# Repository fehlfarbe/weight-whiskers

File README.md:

# weight-whiskers

This is an ESP32 S2 based smart scale that tracks my cat's weight and sends data via MQTT to my smart home. I did the project to automatically track my sick cat's weight when he visits his toilet. Unfortunately he died in August 2023. So this is dedicated to you, my beloved Schneeball 🖤🌈

Schneeball testing the scale

# Hardware

I made a prototype on a solder board with an ESP32 S2 breakout board. I like the WEMOS S2 mini which is very small. You might have to change some pins. Or just use the gerber files and make the PCB. You can find the KiCAD project and gerber files at [hardware](hardware/).

You can connect all load cells that are compatible with the HX711 IC. I'm using [four cells that can measure up to 50Kg](https://de.aliexpress.com/item/1005004867068245.html) because it's easier to keep a big cat toilet balanced.

## Schematic

[PDF](doc/pcb_schematic.pdf)

## 2D plot

#### Front

**Important:** Check the VCC and GND position of the display! Some displays have GND on the first pin and VCC on the second like in the rendered image. You need a display with `VCC  | GND | SCL | SDA` pinout as you can see in the 2D front plot.

#### Back

## 3D rendering

#### Front

#### Back

## Images

# Software

## Installation

Just install [PlatformIO](https://platformio.org/), clone the project, connect the device and run:
`pio run -t upload -e esp32s` to upload the sketch and `pio run -t uploadfs -e esp32s2` to upload the filesystem that contains the config file and web interface. Use the environment `-e esp32s2_ota` if you want to update the device via WiFi.
WARNING: When you update the filesystem you will overwrite the config file and measurements. So please backup it first!

# Usage

On first start the weight-whiskers scale will create an access point that has a config page at <http://192.168.4.1> where you can connect to your local WiFi. If the connection was successful you can find the actual web interface at <http://weight-whiskers.local> in your local network or check your internet router page to get the local IP address.

With a long press on the encoder you can calibrate the load cells with a known weight. The default weight is 500g but you can change it by rotating the encoder (or set it up on the web interface). Just follow the instructions on the display. To tare the scale just short press (<1s) the encoder button.

You can configure the `scale minimum weight` on the web interface. If the cat enters the scale, the LED lights up yellow and the scale measures the weight (with standard deviation) and duration until the cat left the scale. Afterwards the LED lights up green and the result will be stored in the CSV file and sent via MQTT message. If you connected the buzzer, a fancy sound will be played :D

## Web interface

On the web interface you can show, delete and down- and upload the data. The measurements are stored in a CSV file on the device. You can download it and open it in a text editor or import it with a spreadsheet editor. You can also edit the config and show the scale's live data.

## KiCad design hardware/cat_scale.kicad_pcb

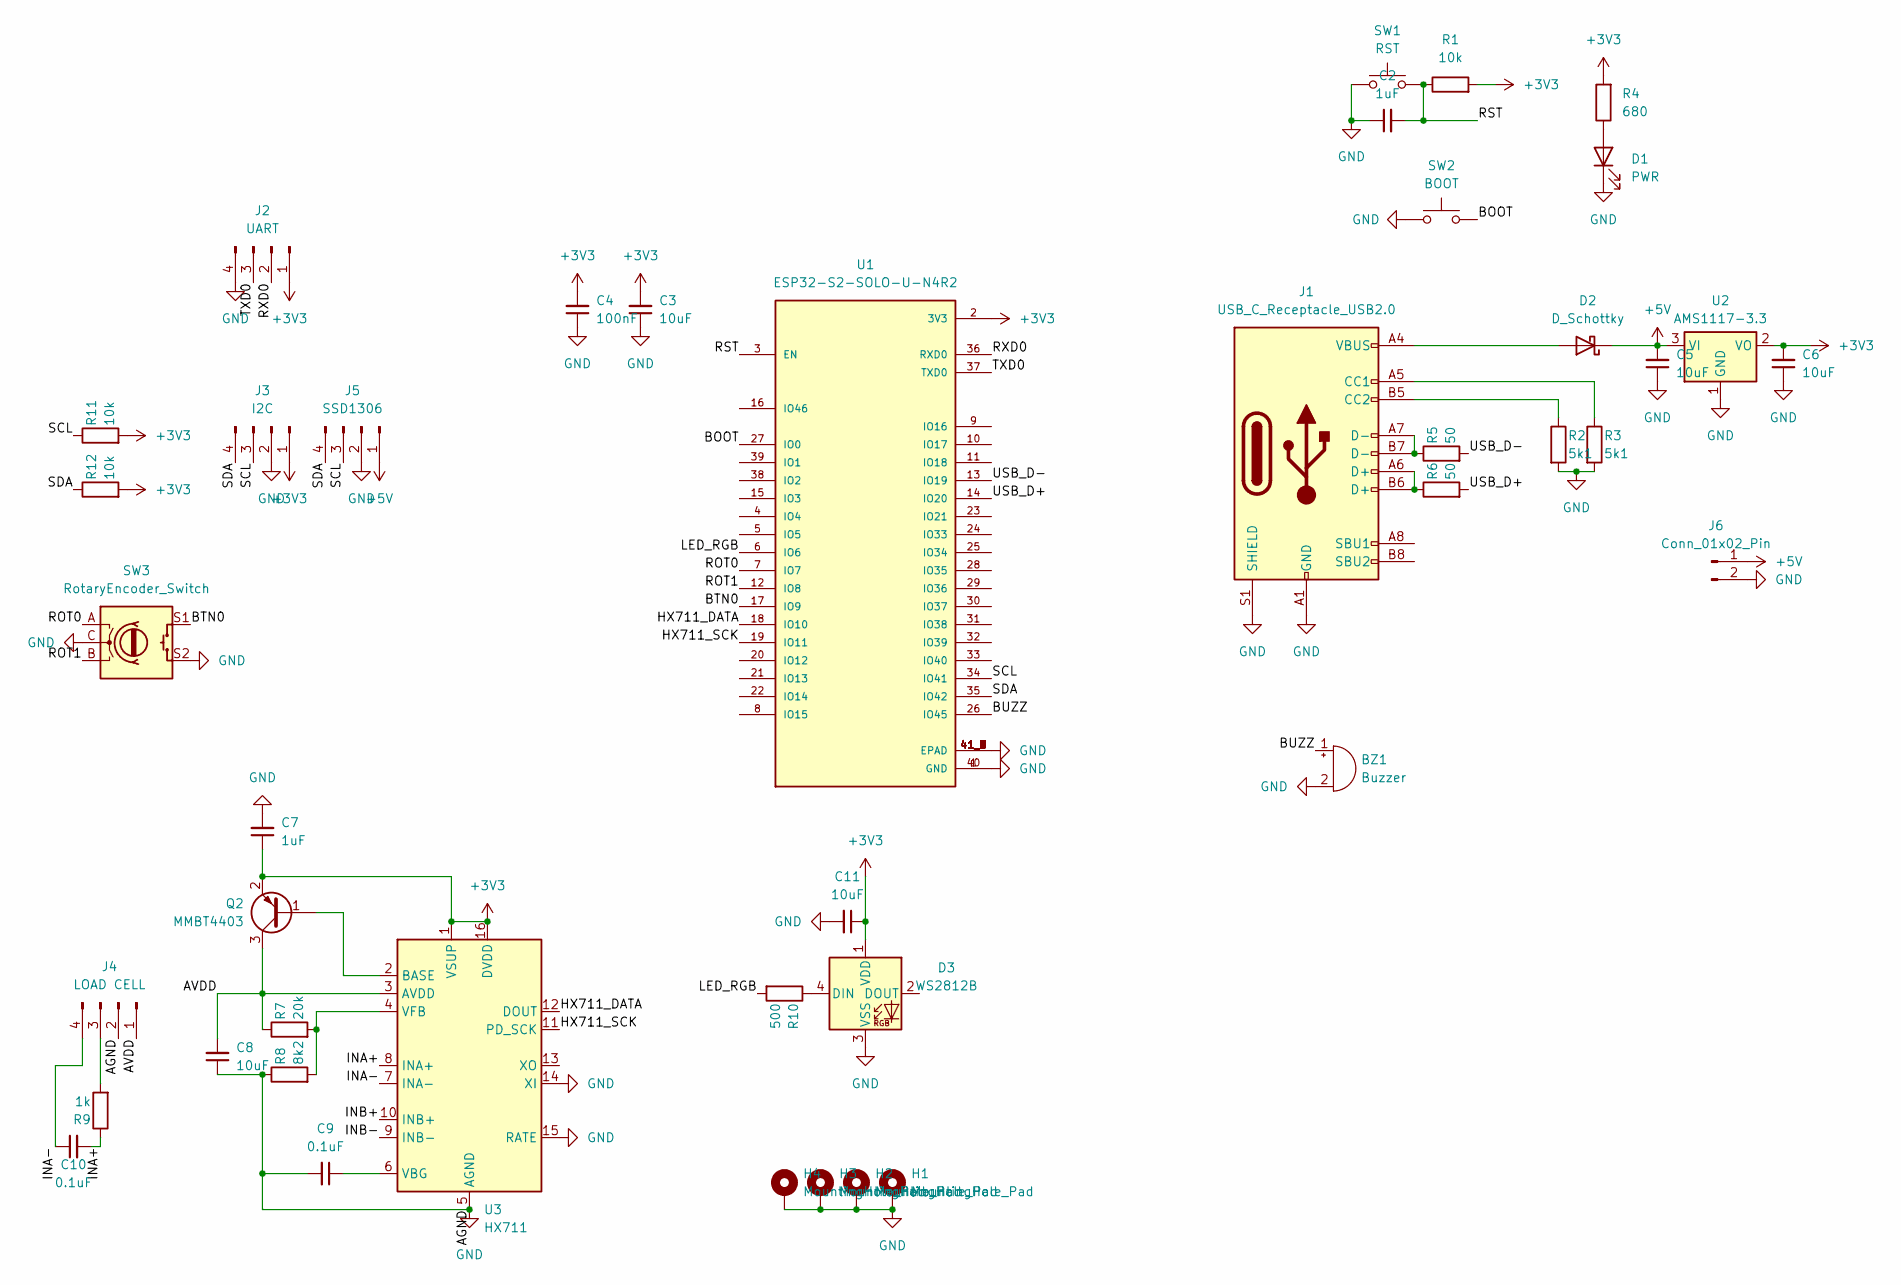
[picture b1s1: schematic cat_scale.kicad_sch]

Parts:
BZ1: Buzzer; Buzzer_Murata_PKMCS0909E
C2, C7: 1uF; C_1206_3216Metric
C3, C5, C6, C8, C11: 10uF; C_1206_3216Metric
C4: 100nF; C_1206_3216Metric
C9, C10: 0.1uF; C_1206_3216Metric
D1: PWR; LED_0805_2012Metric
D2: D_Schottky; D_SOD-323
D3: WS2812B; LED_WS2812B_PLCC4_5.0x5.0mm_P3.2mm
H1, H2, H3, H4: MountingHole_Pad; MountingHole_3.2mm_M3_Pad
J1: USB_C_Receptacle_USB2.0; USB_C_Receptacle_JAE_DX07S016JA1R1500
J2: UART; PinHeader_1x04_P2.54mm_Vertical
J3: I2C; PinHeader_1x04_P2.54mm_Vertical
J4: LOAD CELL; PinHeader_1x04_P2.54mm_Vertical
J5: SSD1306; 128x64OLED
J6: Conn_01x02_Pin; PinHeader_1x02_P2.54mm_Vertical
Q2: MMBT4403; SOT-23
R1, R11, R12: 10k; R_1206_3216Metric
R2, R3: 5k1; R_1206_3216Metric
R4: 680; R_1206_3216Metric
R5, R6: 50; R_1206_3216Metric
R7: 20k; R_1206_3216Metric
R8: 8k2; R_1206_3216Metric
R9: 1k; R_1206_3216Metric
R10: 500; R_1206_3216Metric
SW1: RST; SW_SPST_CK_RS282G05A3
SW2: BOOT; SW_SPST_CK_RS282G05A3
SW3: RotaryEncoder_Switch; RotaryEncoder_Alps_EC12E-Switch_Vertical_H20mm
U1: ESP32-S2-SOLO-U-N4R2; XCVR_ESP32-S2-SOLO-U-N4R2; PARTREV 1.4
U2: AMS1117-3.3; SOT-223-3_TabPin2
U3: HX711; SOP-16_3.9x9.9mm_P1.27mm

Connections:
+3V3: C3.2, C4.2, C6.2, C7.1, C11.1, D3.1 (VDD), J2.1, J3.1, Q2.2 (E), R1.2, R4.2, R11.2, R12.2, U1.2 (3V3), U2.2 (VO), U3.1 (VSUP), U3.16 (DVDD)
+5V: C5.2, D2.1 (K), J5.1, J6.1, U2.3 (VI)
/AVDD: C8.2, J4.1, Q2.3 (C), R7.1, U3.3 (AVDD)
/BOOT: SW2.2, U1.27 (IO0)
/BTN0: SW3.S1, U1.17 (IO9)
/BUZZ: BZ1.1 (-), U1.26 (IO45)
/HX711_DATA: U1.18 (IO10), U3.12 (DOUT)
/HX711_SCK: U1.19 (IO11), U3.11 (PD_SCK)
/INA+: C10.2, R9.1, U3.8 (INA+)
/INA-: C10.1, J4.4, U3.7 (INA-)
/INB+: U3.10 (INB+)
/INB-: U3.9 (INB-)
/LED_RGB: R10.2, U1.6 (IO6)
/ROT0: SW3.A, U1.7 (IO7)
/ROT1: SW3.B, U1.12 (IO8)
/RST: C2.2, R1.1, SW1.2, U1.3 (EN)
/RXD0: J2.2, U1.36 (RXD0)
/SCL: J3.3, J5.3, R11.1, U1.34 (IO41)
/SDA: J3.4, J5.4, R12.1, U1.35 (IO42)
/TXD0: J2.3, U1.37 (TXD0)
/USB_D+: R6.2, U1.14 (IO20)
/USB_D-: R5.2, U1.13 (IO19)
GND: BZ1.2 (+), C2.1, C3.1, C4.1, C5.1, C6.1, C7.2, C8.1, C9.2, C11.2, D1.1 (K), D3.3 (VSS), H1.1, H2.1, H3.1, H4.1, J1.A1 (GND), J1.A12 (GND), J1.B1 (GND), J1.B12 (GND), J1.S1 (SHIELD), J2.4, J3.2, J4.2, J5.2, J6.2, R2.2, R3.2, R8.1, SW1.1, SW2.1, SW3.C, SW3.S2, U1.1 (GND), U1.40 (GND), U1.41_1 (EPAD), U1.41_2 (EPAD), U1.41_3 (EPAD), U1.41_4 (EPAD), U1.41_5 (EPAD), U1.41_6 (EPAD), U1.41_7 (EPAD), U1.41_8 (EPAD), U1.41_9 (EPAD), U2.1 (GND), U3.5 (AGND), U3.14 (XI), U3.15 (RATE)
unnamed: D1.2 (A), R4.1
unnamed: D2.2 (A), J1.A4 (VBUS), J1.A9 (VBUS), J1.B4 (VBUS), J1.B9 (VBUS)
unnamed: D3.4 (DIN), R10.1
unnamed: J1.A5 (CC1), R3.1
unnamed: J1.B5 (CC2), R2.1
unnamed: J1.A6 (D+), J1.B6 (D+), R6.1
unnamed: J1.A7 (D-), J1.B7 (D-), R5.1
unnamed: J4.3, R9.2
unnamed: Q2.1 (B), U3.2 (BASE)
unnamed: C9.1, U3.6 (VBG)
unnamed: R7.2, R8.2, U3.4 (VFB)

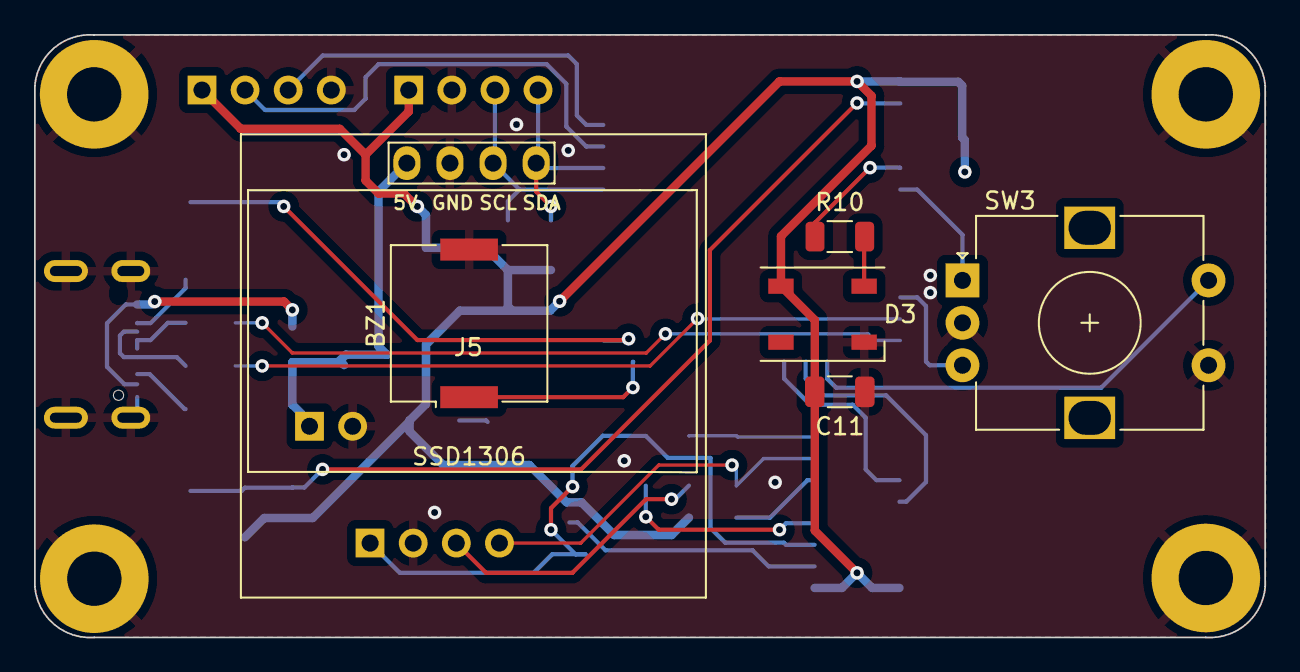
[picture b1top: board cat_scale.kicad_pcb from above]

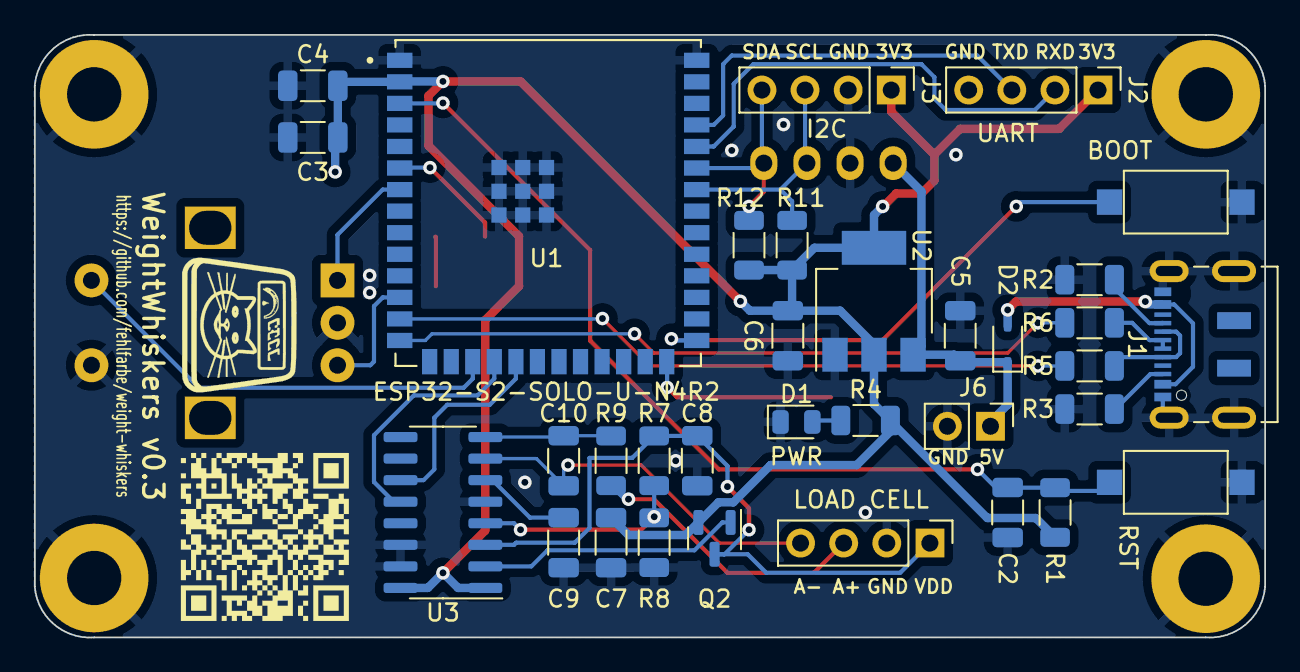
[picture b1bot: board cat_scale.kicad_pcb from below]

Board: 2 copper layers, 72.5 x 35.5 mm, 43 parts (33 on the bottom side), 32 nets.

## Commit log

2023-07-14 Added config file handling and OTA
2023-07-14 Added first code
2023-07-14 Added PCB layout
2023-08-01 * Moved to ESPAsyncWebserver * Created React App for config (wip)
2023-08-02 * Working React App for config
2023-08-02 Fixed PCB design
2023-08-02 Create react app on buildfs/uploadfs
2023-08-10 * Cleanup dependencies * Enabled ArduinoOTA * Added WebSocket sender for live data * Improved button handling for tare/calibration
2023-08-10 Added graphs for live values and measurements history to webinterface
2023-08-13 * Added main menu to web interface * Added system info to web interface * Some refactoring (better plots etc.) * favicon has white background
2023-08-26 * Moved SVG to component to prevent too long generated filename for LittleFS * Added system statistics to config page * WIP: Added checkboxes to delete measurements
2023-08-26 * Refactoring: moved display stuff to class * measurements contain duration instead of variance * added minimum presence time to config * added support for buzzer that plays a sound after cat finishe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
2023-08-26 * PCB: Added buzzer
2023-09-15 * Added encoder support to change calibration weight * Added buzzer that plays a melody on start/measurement
2023-09-15 Updated PCB and added images of the PCB to README
2023-09-15 Added new arguments to encoder constructor
2023-12-03 CSV upload is working
2023-12-05 Connect live measurements WebSocket to current host
2023-12-10 Added standard deviation to CSV file and implemented selective deletion of measurements in the web interface.
2023-12-10 Updated PCB and README
2024-01-16 * Fixed bug in WiFi reconnect * Saving measurement with lowest std deviation * Plotting std deviation hose in web interface * Saving measurement with lowest std deviation
2024-02-14 Added simple time filter for web interface Measurements page
2024-02-14 Additional time filter for web interface Measurements page
2024-02-14 Fixed negative / too big values for droppings in csv data
2024-02-14 Added weight of droppings to table in measurements
2024-02-15 Fixed date format bug in filtering measurements
2024-02-15 Removed horizontal scrollbar from measurement table
2024-10-10 * Updated ESPAsyncWebServer * added some debug output for WebSocket * added custom partitions.csv
2025-01-11 Added reboot API command
2025-01-23 Set cpp coding style
2025-01-23 Updated weblibs
2025-01-23 Added histogram to measurements web page
2025-01-23 Added latest build of web page
2025-10-27 Fix crashes because off filled MQTT measurements buffer
2025-10-27 Added moving average for measurements page on web interface
2025-10-29 Added data aggregation for "all data" and "last three months"
2025-10-29 Set fixed espressif platform version
2025-10-29 Calculate number of labels based on window width
2025-11-07 Updated libs and config
2025-11-07 Added new fields to mqtt config (enabled, user, pass) and moved mqtt handling to own task
2025-11-08 Added "loading bar" to visualize at which time the measurement will be valid and stored to flash
2026-06-12 Updated ESPAsyncWebServer
2026-06-12 added filter for unreasonable measurements
2026-06-12 Moved CSV download and upload to "config" section
